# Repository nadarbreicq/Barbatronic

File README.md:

# Barbatronic

Ce git répertorie la plupart des projets présentés lors des Lives Twitch et des vidéos Youtubes de la chaine Barbatronic. Pour les projets liés à la Coupe de France de robotique, vosu pouvez retrouver les sources dans les repo de l'équipe des Karibous (https://github.com/LesKaribous)

Les projets sont triés par type plutôt que par numéro de live ou de vidéos car un projet peut être présenté plusieurs fois sur plusieurs supports différents.

Tous les projets de la chaine ne sont pas (encore) sur ce repo. Je suis en train de rapatrier les projets depuis Fusion360 et Egale, mais cela peut prendre un peu de temps. Si il vous manque un projet, n'hésitez pas à me contacter.

## Logiciels utilisés :

FreeCAD 0.19 de Real thunder : https://github.com/realthunder/FreeCAD_assembly3/releases/tag/0.11

Inkscape 1.0.1 : https://inkscape.org/release/inkscape-1.0.1/

K40 Whisperer : https://www.scorchworks.com/K40whisperer/k40whisperer.html

Eagle : https://www.autodesk.fr/products/eagle

Cura : https://ultimaker.com/fr/software/ultimaker-cura

## Socials :

Youtube   : https://www.youtube.com/barbatroniclive

Twitch    : https://www.twitch.tv/barbatroniclive

Twitter   : https://twitter.com/barbatronic

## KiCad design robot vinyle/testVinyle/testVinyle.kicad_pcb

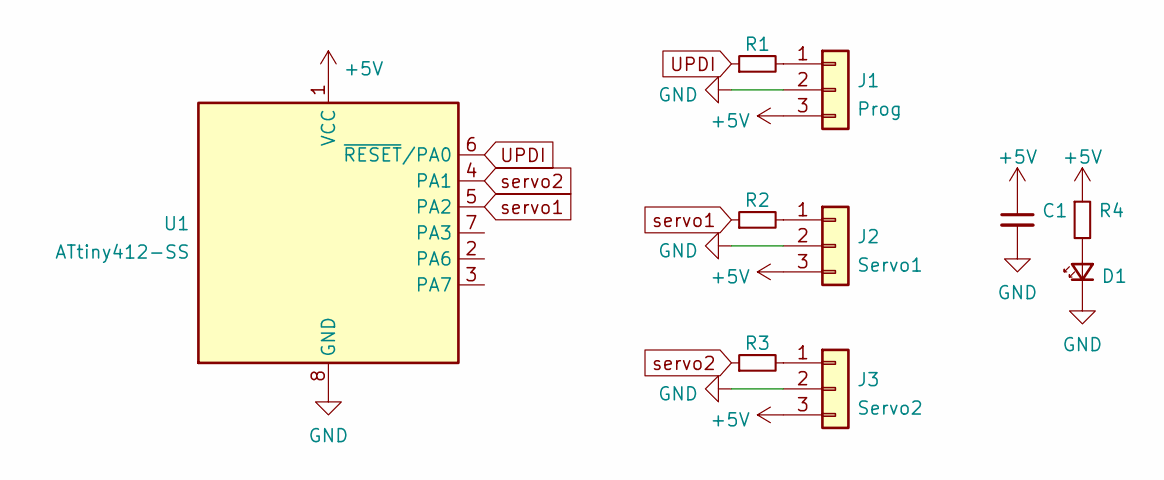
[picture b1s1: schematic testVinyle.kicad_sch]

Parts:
C1: C_Small; C_1206_3216Metric_Pad1.33x1.80mm_HandSolder
D1: LED_Small; LED_1210_3225Metric_Pad1.42x2.65mm_HandSolder
J1: Prog; PinHeader_1x03_22.54mm_Horizontal_SMD_Line
J2: Servo1; PinHeader_1x03_22.54mm_Horizontal_SMD_Line
J3: Servo2; PinHeader_1x03_22.54mm_Horizontal_SMD_Line
R1, R2, R3, R4: R_Small; R_1206_3216Metric_Pad1.30x1.75mm_HandSolder
U1: ATtiny412-SS; SOIC-8_3.9x4.9mm_P1.27mm

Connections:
+5V: C1.1, J1.3, J2.3, J3.3, R4.1, U1.1 (VCC)
GND: C1.2, D1.1 (K), J1.2, J2.2, J3.2, U1.8 (GND)
unnamed: D1.2 (A), R4.2
unnamed: J1.1, R1.2
unnamed: J2.1, R2.2
unnamed: J3.1, R3.2
UPDI: R1.1, U1.6 (~RESET/PA0)
servo1: R2.1, U1.5 (PA2)
servo2: R3.1, U1.4 (PA1)

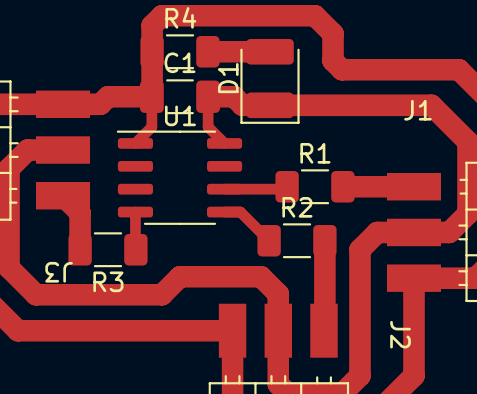
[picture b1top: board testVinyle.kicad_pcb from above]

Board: 2 copper layers, 10 parts (0 on the bottom side), 9 nets.

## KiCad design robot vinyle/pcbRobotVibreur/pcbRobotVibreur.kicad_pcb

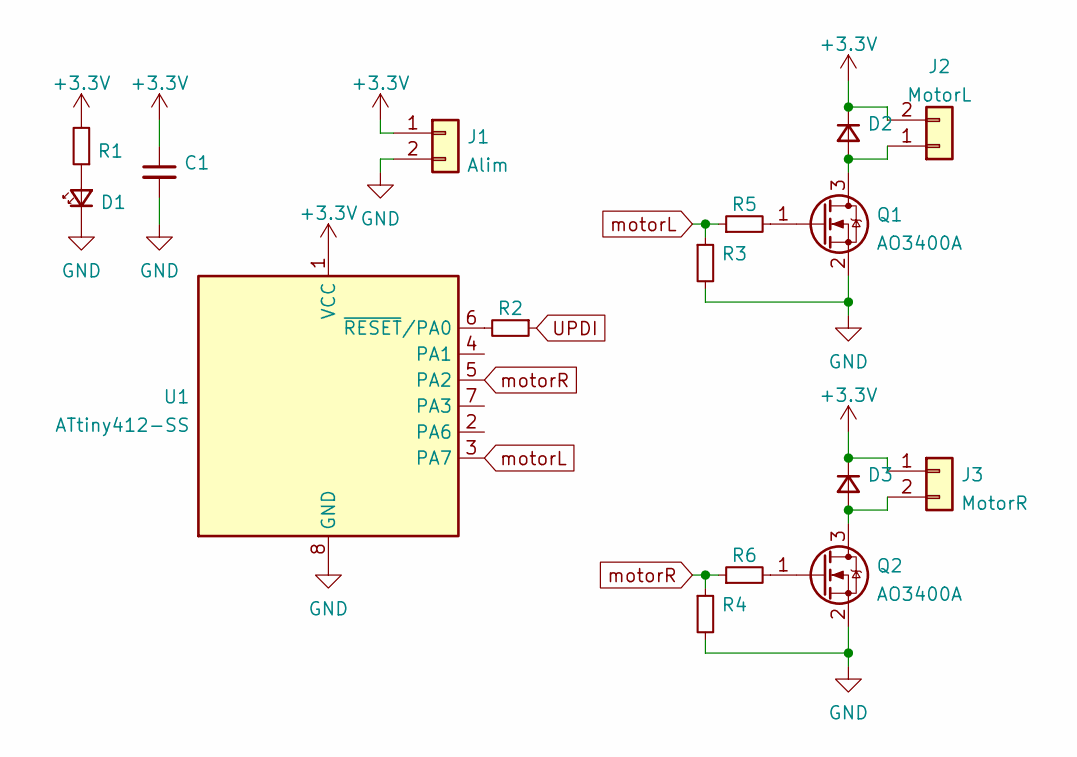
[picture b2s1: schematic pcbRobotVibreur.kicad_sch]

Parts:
C1: C_Small; C_1206_3216Metric_Pad1.33x1.80mm_HandSolder
D1: LED_Small; LED_1206_3216Metric_Pad1.42x1.75mm_HandSolder
D2, D3: D_Small; D_SMB_Handsoldering
J1: Alim; PinHeader_1x02_2.54mm_Horizontal_SMD_Line
J2: MotorL; PinHeader_1x02_2.54mm_Horizontal_SMD_Line
J3: MotorR; PinHeader_1x02_2.54mm_Horizontal_SMD_Line
Q1, Q2: AO3400A; SOT-23
R1, R2, R3, R4, R5, R6: R_Small; R_1206_3216Metric_Pad1.30x1.75mm_HandSolder
U1: ATtiny412-SS; SOIC-8_3.9x4.9mm_P1.27mm

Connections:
+3V3: C1.1, D2.1 (K), D3.1 (K), J1.1, J2.2, J3.1, R1.2, U1.1 (VCC)
GND: C1.2, D1.1 (K), J1.2, Q1.2 (S), Q2.2 (S), R3.2, R4.2, U1.8 (GND)
unnamed: D1.2 (A), R1.1
unnamed: D2.2 (A), J2.1, Q1.3 (D)
unnamed: D3.2 (A), J3.2, Q2.3 (D)
unnamed: Q1.1 (G), R5.2
unnamed: Q2.1 (G), R6.2
unnamed: R2.2, U1.6 (~RESET/PA0)
UPDI: R2.1
motorL: R3.1, R5.1, U1.3 (PA7)
motorR: R4.1, R6.1, U1.5 (PA2)

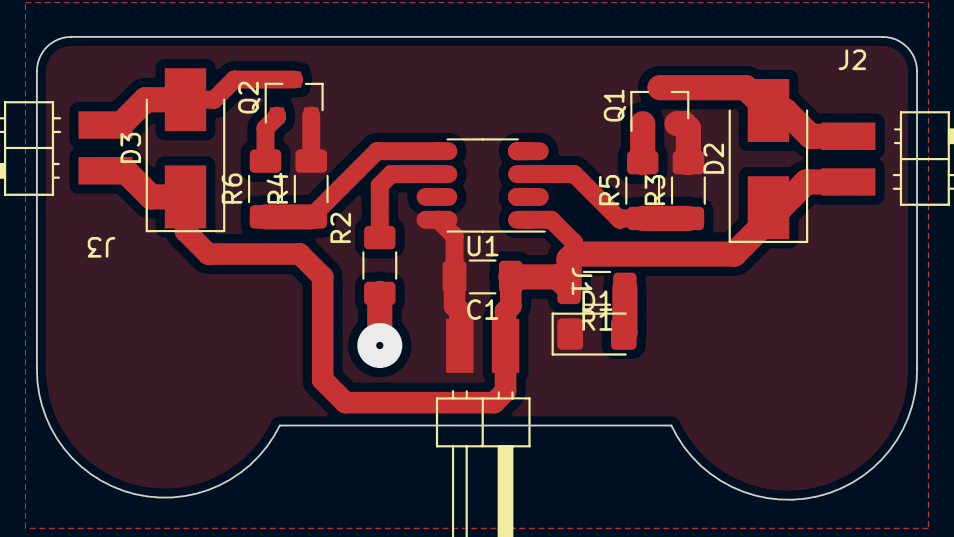
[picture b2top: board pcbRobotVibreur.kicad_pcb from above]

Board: 2 copper layers, 48.9 x 25.7 mm, 16 parts (0 on the bottom side), 10 nets.

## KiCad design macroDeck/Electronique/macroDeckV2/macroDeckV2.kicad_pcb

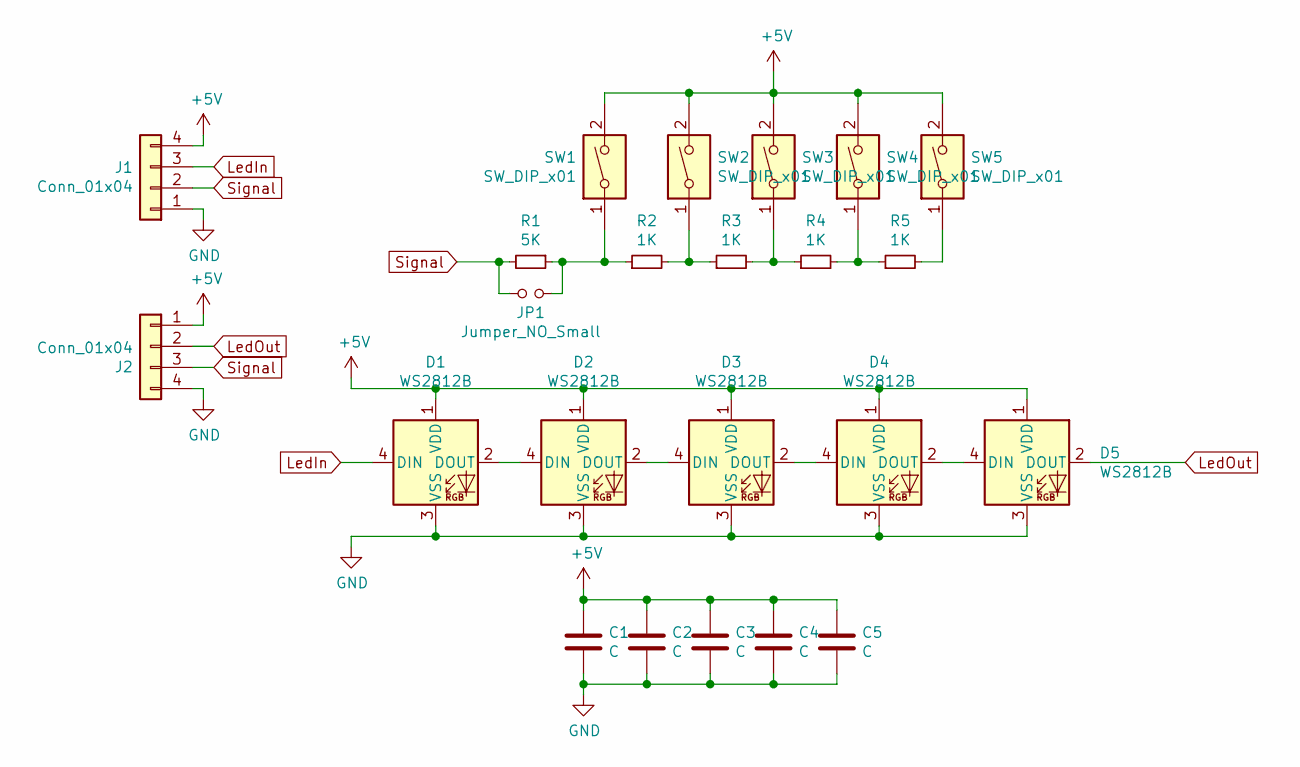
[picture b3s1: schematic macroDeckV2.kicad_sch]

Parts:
C1, C2, C3, C4, C5: C; C_1206_3216Metric_Pad1.33x1.80mm_HandSolder
D1, D2, D3, D4, D5: WS2812B; LED_WS2812B_PLCC4_5.0x5.0mm_P3.2mm
J1, J2: Conn_01x04; PinHeader_1x04_22.54mm_Horizontal_SMD_Line
JP1: Jumper_NO_Small; SolderJumper-2_P1.3mm_Open_Pad1.0x1.5mm
R1: 5K; R_1206_3216Metric_Pad1.30x1.75mm_HandSolder
R2, R3, R4, R5: 1K; R_1206_3216Metric_Pad1.30x1.75mm_HandSolder
SW1, SW2, SW3, SW4, SW5: SW_DIP_x01; SW_Push_1P1T_NO_6x6mm_H9.5mm

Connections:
+5V: C1.1, C2.1, C3.1, C4.1, C5.1, D1.1 (VDD), D2.1 (VDD), D3.1 (VDD), D4.1 (VDD), D5.1 (VDD), J1.4, J2.1, SW1.2, SW2.2, SW3.2, SW4.2, SW5.2
GND: C1.2, C2.2, C3.2, C4.2, C5.2, D1.3 (VSS), D2.3 (VSS), D3.3 (VSS), D4.3 (VSS), D5.3 (VSS), J1.1, J2.4
LedIn: D1.4 (DIN), J1.3
LedOut: D5.2 (DOUT), J2.2
unnamed: D1.2 (DOUT), D2.4 (DIN)
unnamed: D2.2 (DOUT), D3.4 (DIN)
unnamed: D3.2 (DOUT), D4.4 (DIN)
unnamed: D4.2 (DOUT), D5.4 (DIN)
unnamed: JP1.2, R1.1, R2.1, SW1.1
unnamed: R2.2, R3.1, SW2.1
unnamed: R3.2, R4.1, SW3.1
unnamed: R4.2, R5.1, SW4.1
unnamed: R5.2, SW5.1
Signal: J1.2, J2.3, JP1.1, R1.2

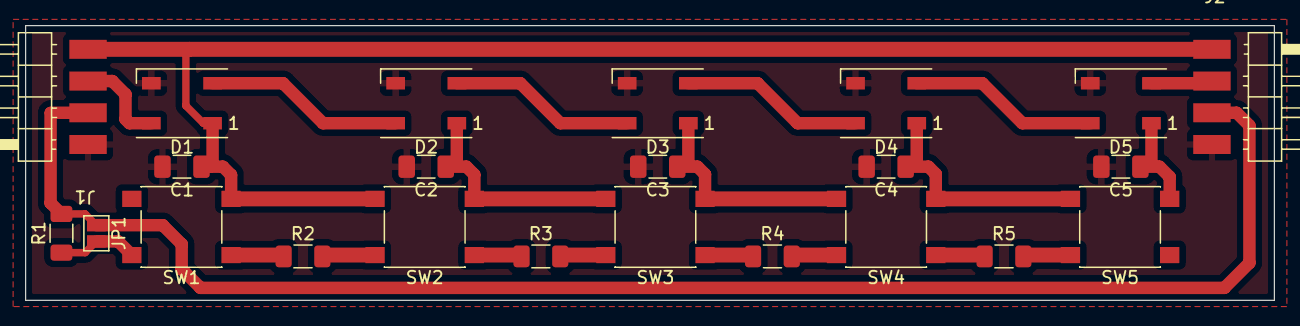
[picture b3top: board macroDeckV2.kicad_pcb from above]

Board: 2 copper layers, 100.0 x 22.0 mm, 23 parts (0 on the bottom side), 14 nets.

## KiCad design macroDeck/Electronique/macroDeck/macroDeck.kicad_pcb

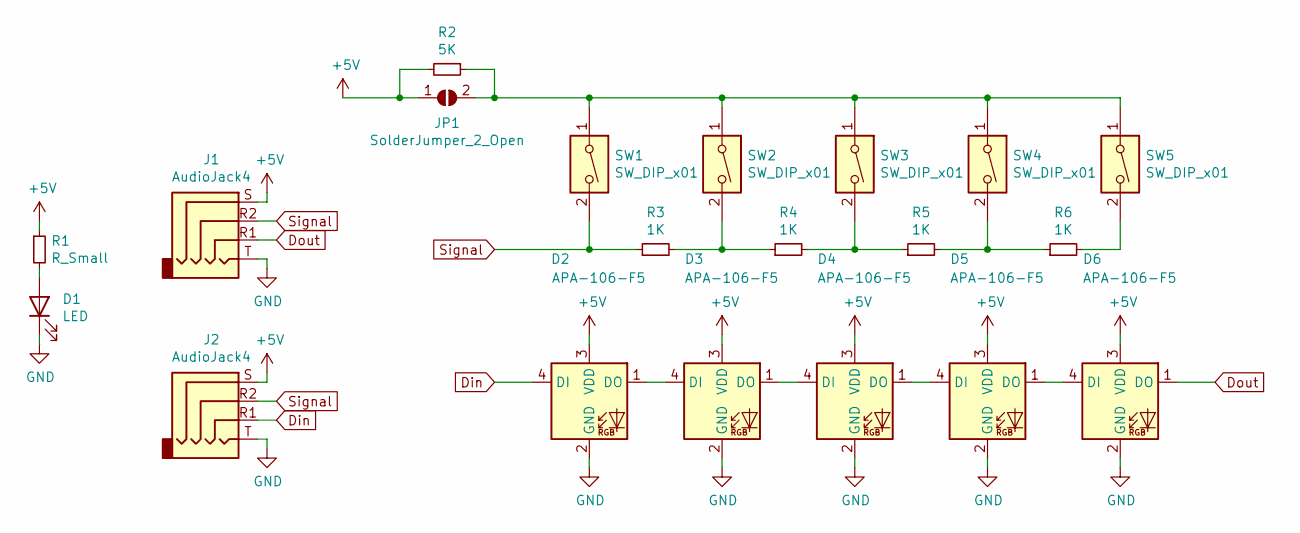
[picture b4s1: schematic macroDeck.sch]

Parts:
D1: LED; LED_D5.0mm
D2, D3, D4, D5, D6: APA-106-F5; LED_D5.0mm-4_RGB
J1, J2: AudioJack4; Jack_3.5mm_PJ320D_Horizontal
JP1: SolderJumper_2_Open; SolderJumper-2_P1.3mm_Open_RoundedPad1.0x1.5mm
R1: R_Small; R_Axial_DIN0204_L3.6mm_D1.6mm_P5.08mm_Horizontal
R2: 5K; R_Axial_DIN0204_L3.6mm_D1.6mm_P5.08mm_Horizontal
R3, R4, R5, R6: 1K; R_Axial_DIN0204_L3.6mm_D1.6mm_P5.08mm_Horizontal
SW1, SW2, SW3, SW4, SW5: SW_DIP_x01; SW_Cherry_MX_1.00u_Plate

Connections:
+5V: D2.3 (VDD), D3.3 (VDD), D4.3 (VDD), D5.3 (VDD), D6.3 (VDD), J1.S, J2.S, JP1.1 (A), R1.1, R2.2
Din: D2.4 (DI), J2.R1
Dout: D6.1 (DO), J1.R1
GND: D1.1 (K), D2.2 (GND), D3.2 (GND), D4.2 (GND), D5.2 (GND), D6.2 (GND), J1.T, J2.T
unnamed: D1.2 (A), R1.2
unnamed: D2.1 (DO), D3.4 (DI)
unnamed: D3.1 (DO), D4.4 (DI)
unnamed: D4.1 (DO), D5.4 (DI)
unnamed: D5.1 (DO), D6.4 (DI)
unnamed: JP1.2 (B), R2.1, SW1.1, SW2.1, SW3.1, SW4.1, SW5.1
unnamed: R3.2, R4.1, SW2.2
unnamed: R4.2, R5.1, SW3.2
unnamed: R5.2, R6.1, SW4.2
unnamed: R6.2, SW5.2
Signal: J1.R2, J2.R2, R3.1, SW1.2

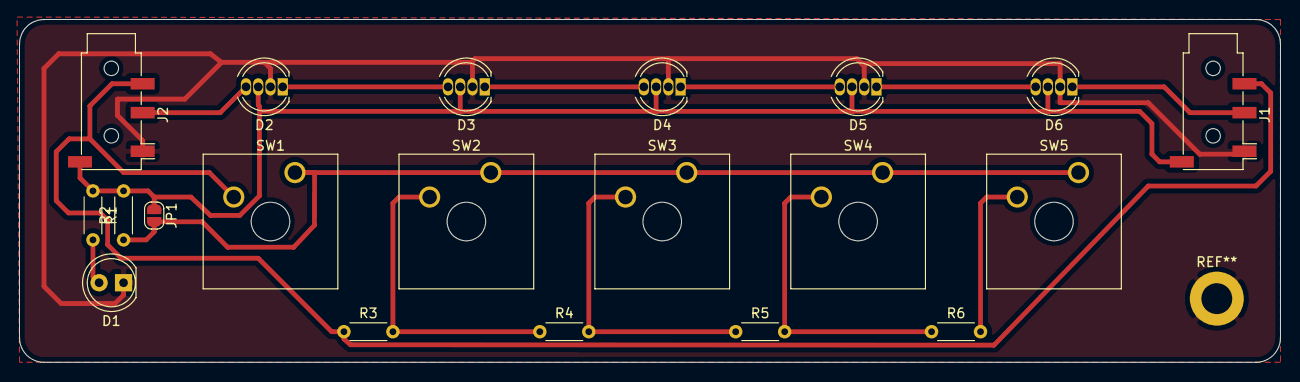
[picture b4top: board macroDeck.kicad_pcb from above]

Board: 2 copper layers, 130.8 x 35.6 mm, 20 parts (0 on the bottom side), 15 nets.

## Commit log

2020-11-18 typo
2020-11-19 first upload
2020-11-23 live 65
2020-11-23 Update list
2020-11-23 update prices
2020-11-23 fix table
2020-12-01 add k40.se site
2020-12-01 add infos
2020-12-07 live 67
2020-12-13 live 68
2020-12-17 new StickVise hack
2020-12-17 change directories
2020-12-23 creation
2020-12-23 update description and image
2021-01-10 multi upload
2021-01-11 live 71
2021-01-14 add ref
2021-01-31 Set theme jekyll-theme-minimal
2021-01-31 Create CNAME
2021-01-31 Update CNAME
2021-02-08 huge upload
2021-02-08 Add KiCAD files autosave
2021-03-02 hovercraft project
2021-03-02 Add support bobine
2021-03-02 Change repo
2021-03-02 BoxGenerator first commit
2021-03-06 bad constraint
2021-03-06 Cadres des vues
    Affichage du cadre des vues activé par défaut dans le fichier.
2021-11-28 projet #2
